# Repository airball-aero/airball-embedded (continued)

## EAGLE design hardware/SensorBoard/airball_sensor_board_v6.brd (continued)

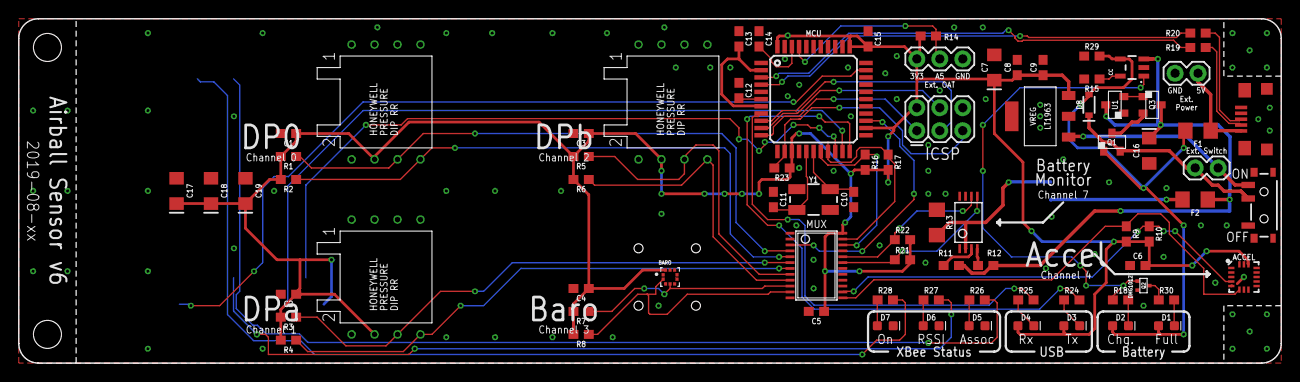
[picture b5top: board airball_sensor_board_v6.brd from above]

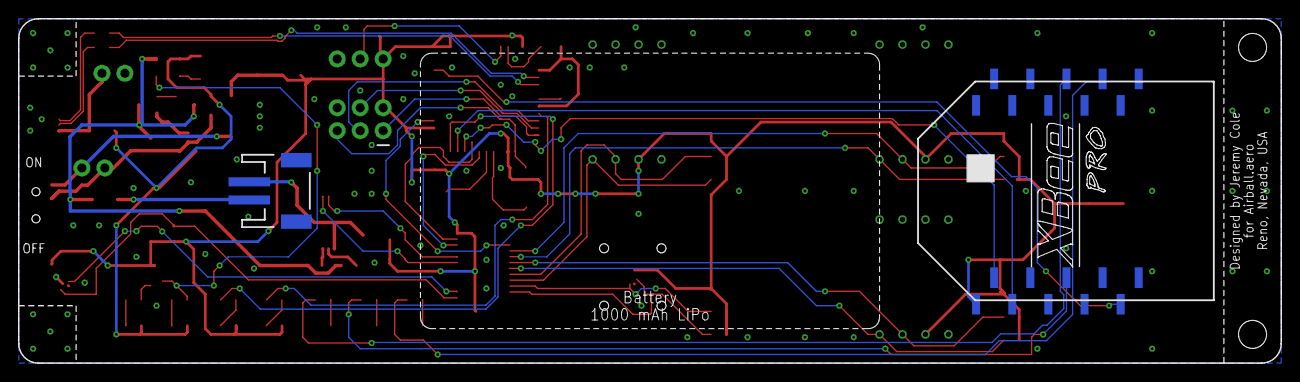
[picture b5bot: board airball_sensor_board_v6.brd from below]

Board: 2 copper layers, 139.7 x 38.1 mm, 83 parts (3 on the bottom side), 60 nets.

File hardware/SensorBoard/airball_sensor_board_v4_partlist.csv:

Partlist

Exported from airball_sensor_board_v4.brd at 2/25/20 10:12 PM

EAGLE Version 9.5.2 Copyright (c) 1988-2019 Autodesk, Inc.

Assembly variant: 

Part      Value               Package                Library             Position (mil)        Orientation

BARO                          ALLSENSORS_E1BD        airball             (1562.5 375)          R270
BM        DS2782              TSSOP8                 airball             (4725 825)            R0
C1        0.1uF               0603                   SparkFun-Capacitors (1175 1425)           R180
C2        0.1uF               0603                   SparkFun-Capacitors (1175 675)            R180
C3        0.1uF               0603                   SparkFun-Capacitors (2425 1425)           R180
C4        0.1uF               0603                   SparkFun-Capacitors (2425 675)            R180
C5        0.1uF               0603                   SparkFun-Capacitors (3475 225)            R180
C6        0.1uF               0603                   SparkFun-Capacitors (4875 425)            R180
C7        10uF                EIA3216                SparkFun-Capacitors (4250 1287.5)         R270
C8        1.0uF               0603                   SparkFun-Capacitors (4350 1287.5)         R90
C9        0.1uF               0603                   SparkFun-Capacitors (4462.5 1287.5)       R90
C10       22pF                0603                   SparkFun-Capacitors (3637.5 737.5)        R90
C11       22pF                0603                   SparkFun-Capacitors (3287.5 737.5)        R270
C12       1.0uF               0603                   SparkFun-Capacitors (3137.5 1187.5)       R270
C13       1.0uF               0603                   SparkFun-Capacitors (3137.5 1412.5)       R270
C14       0.1uF               0603                   SparkFun-Capacitors (3225 1412.5)         R270
C15       0.1uF               0603                   SparkFun-Capacitors (3700 1412.5)         R270
C16       10uF                EIA3216                SparkFun-Capacitors (4975 1037.5)         R90
C17       10uF                EIA3216                SparkFun-Capacitors (687.5 750)           R270
C18       10uF                EIA3216                SparkFun-Capacitors (837.5 750)           R270
C19       10uF                EIA3216                SparkFun-Capacitors (987.5 750)           R270
CC        MCP73831            SOT23-5                SparkFun-IC-Power   (4862.5 1175)         R0
D1                            LED-0603               SparkFun-LED        (5000 162.5)          R0
D2                            LED-0603               SparkFun-LED        (4800 162.5)          R0
D3                            LED-0603               SparkFun-LED        (4587.5 162.5)        R0
D4                            LED-0603               SparkFun-LED        (4387.5 162.5)        R0
D5                            LED-0603               SparkFun-LED        (4175 162.5)          R0
D6                            LED-0603               SparkFun-LED        (3975 162.5)          R0
D7                            LED-0603               SparkFun-LED        (3775 162.5)          R0
DP0                           ALLSENSORS_E1BD        airball             (1562.5 1125)         R270
DPA                           ALLSENSORS_E1BD        airball             (2812.5 1125)         R270
DPB                           ALLSENSORS_E1BD        airball             (2812.5 375)          R270
EXT_OAT                       1X03                   SparkFun-Connectors (3912.5 1325)         R0
EXT_POWER                     1X02                   SparkFun-Connectors (5137.5 1262.5)       R180
EXT_SW                        1X02                   SparkFun-Connectors (5125 850)            R0
F1        6V/0.5A             1206                   SparkFun-Fuses      (5137.5 1012.5)       R180
F2        6V/0.5A             1206                   SparkFun-Fuses      (5125 712.5)          R0
ICSP      AVR_SPI_PROG_3X2PTH 2X3                    SparkFun-Connectors (3912.5 1012.5)       R0
J1                            JST-2-SMD              SparkFun-Connectors (4350 750)            MR270
JP1       USB_MICROB_PLUG     USB_MICRO_B_TYCO       airball             (5437.5 1062.5)       R90
MCU       32U4                TQFP44                 jcole               (3462.5 1150)         R0
MUX                           TSSOP24                airball             (3475 425)            R270
OAT       TMP275              SOIC8                  airball             (5337.5 387.5)        R270
R1        4.7k                0603                   SparkFun-Resistors  (1175 1325)           R180
R2        4.7k                0603                   SparkFun-Resistors  (1175 1225)           R180
R3        4.7k                0603                   SparkFun-Resistors  (1175 575)            R180
R4        4.7k                0603                   SparkFun-Resistors  (1175 475)            R180
R5        4.7k                0603                   SparkFun-Resistors  (2425 1325)           R180
R6        4.7k                0603                   SparkFun-Resistors  (2425 1225)           R180
R7        4.7k                0603                   SparkFun-Resistors  (2425 575)            R180
R8        4.7k                0603                   SparkFun-Resistors  (2425 475)            R180
R9        4.7k                0603                   SparkFun-Resistors  (4825 562.5)          R270
R10       4.7k                0603                   SparkFun-Resistors  (4925 562.5)          R270
R11       1k                  0603                   SparkFun-Resistors  (4537.5 737.5)        R180
R12       470                 0603                   SparkFun-Resistors  (4537.5 662.5)        R180
R13       15m                 1206                   SparkFun-Resistors  (4937.5 837.5)        R0
R14       4.7k                0603                   SparkFun-Resistors  (3962.5 1425)         R180
R15       2.0k                0603                   SparkFun-Resistors  (4737.5 1200)         R90
R16       4.7k                0603                   SparkFun-Resistors  (3687.5 875)          R270
R17       4.7k                0603                   SparkFun-Resistors  (3787.5 875)          R270
R18       330                 0603                   SparkFun-Resistors  (4800 275)            R0
R19       22                  0603                   SparkFun-Resistors  (5137.5 1375)         R180
R20       22                  0603                   SparkFun-Resistors  (5137.5 1437.5)       R180
R21       4.7k                0603                   SparkFun-Resistors  (3850 450)            R0
R22       4.7k                0603                   SparkFun-Resistors  (3850 537.5)          R0
R23       10k                 0603                   SparkFun-Resistors  (3312.5 850)          R180
R24       330                 0603                   SparkFun-Resistors  (4587.5 275)          R0
R25       330                 0603                   SparkFun-Resistors  (4387.5 275)          R0
R26       330                 0603                   SparkFun-Resistors  (4175 275)            R0
R27       330                 0603                   SparkFun-Resistors  (3975 275)            R0
R28       330                 0603                   SparkFun-Resistors  (3775 275)            R0
S1                            SWITCH_SPST_SMD_A      SparkFun-Switches   (5425 687.5)          R270
VREG      LT1963              SOT223-3               airball             (4450 1075)           R90
XBEE      XBEE-PRO-SMD        XBEE-PRO-SMD           airball             (975 750)             MR90
Y1        8MHz                CRYSTAL-SMD-5X3.2-4PAD SparkFun-Clocks     (3462.5 737.5)        R0

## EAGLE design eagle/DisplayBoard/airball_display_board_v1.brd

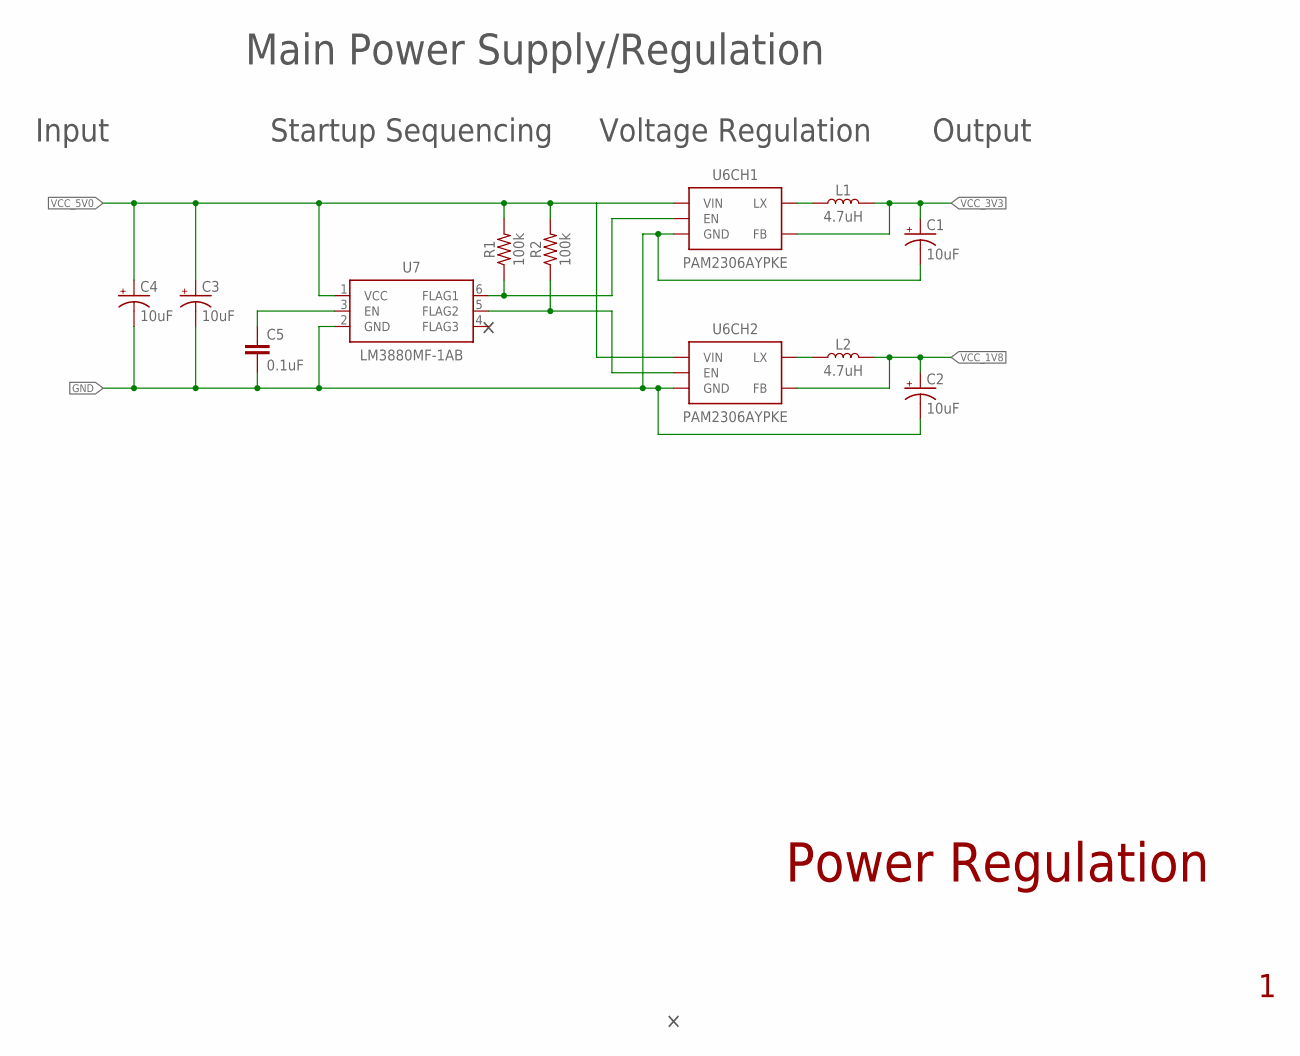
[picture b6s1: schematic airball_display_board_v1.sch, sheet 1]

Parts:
C1, C2, C3, C4: 10uF; EIA3216
C5: 0.1uF; 0603
L1, L2: 4.7uH; INDUCTOR_SMD_4X4MM
R1, R2: 100k; 0603
U6: PAM2306AYPKE; WDFN12
U7: LM3880MF-1AB; SOT23-6

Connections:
EN_1V8: R2.1, U6.12 (EN), U7.5 (FLAG2)
EN_3V3: R1.1, U6.6 (EN), U7.6 (FLAG1)
GND: C1.-, C2.-, C3.-, C4.-, C5.2, U6.3 (GND), U6.9 (GND), U7.2 (GND); also elsewhere on the board
unnamed: L1.1, U6.8 (LX)
unnamed: L2.1, U6.2 (LX)
unnamed: C5.1, U7.3 (EN)
VCC_1V8: C2.+, L2.2, U6.10 (FB); also elsewhere on the board
VCC_3V3: C1.+, L1.2, U6.4 (FB); also elsewhere on the board
VCC_5V0: C3.+, C4.+, R1.2, R2.2, U6.1 (VIN), U6.7 (VIN), U7.1 (VCC); also elsewhere on the board

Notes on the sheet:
Power Regulation
Main Power Supply/Regulation
Startup Sequencing
Voltage Regulation
Input
Output

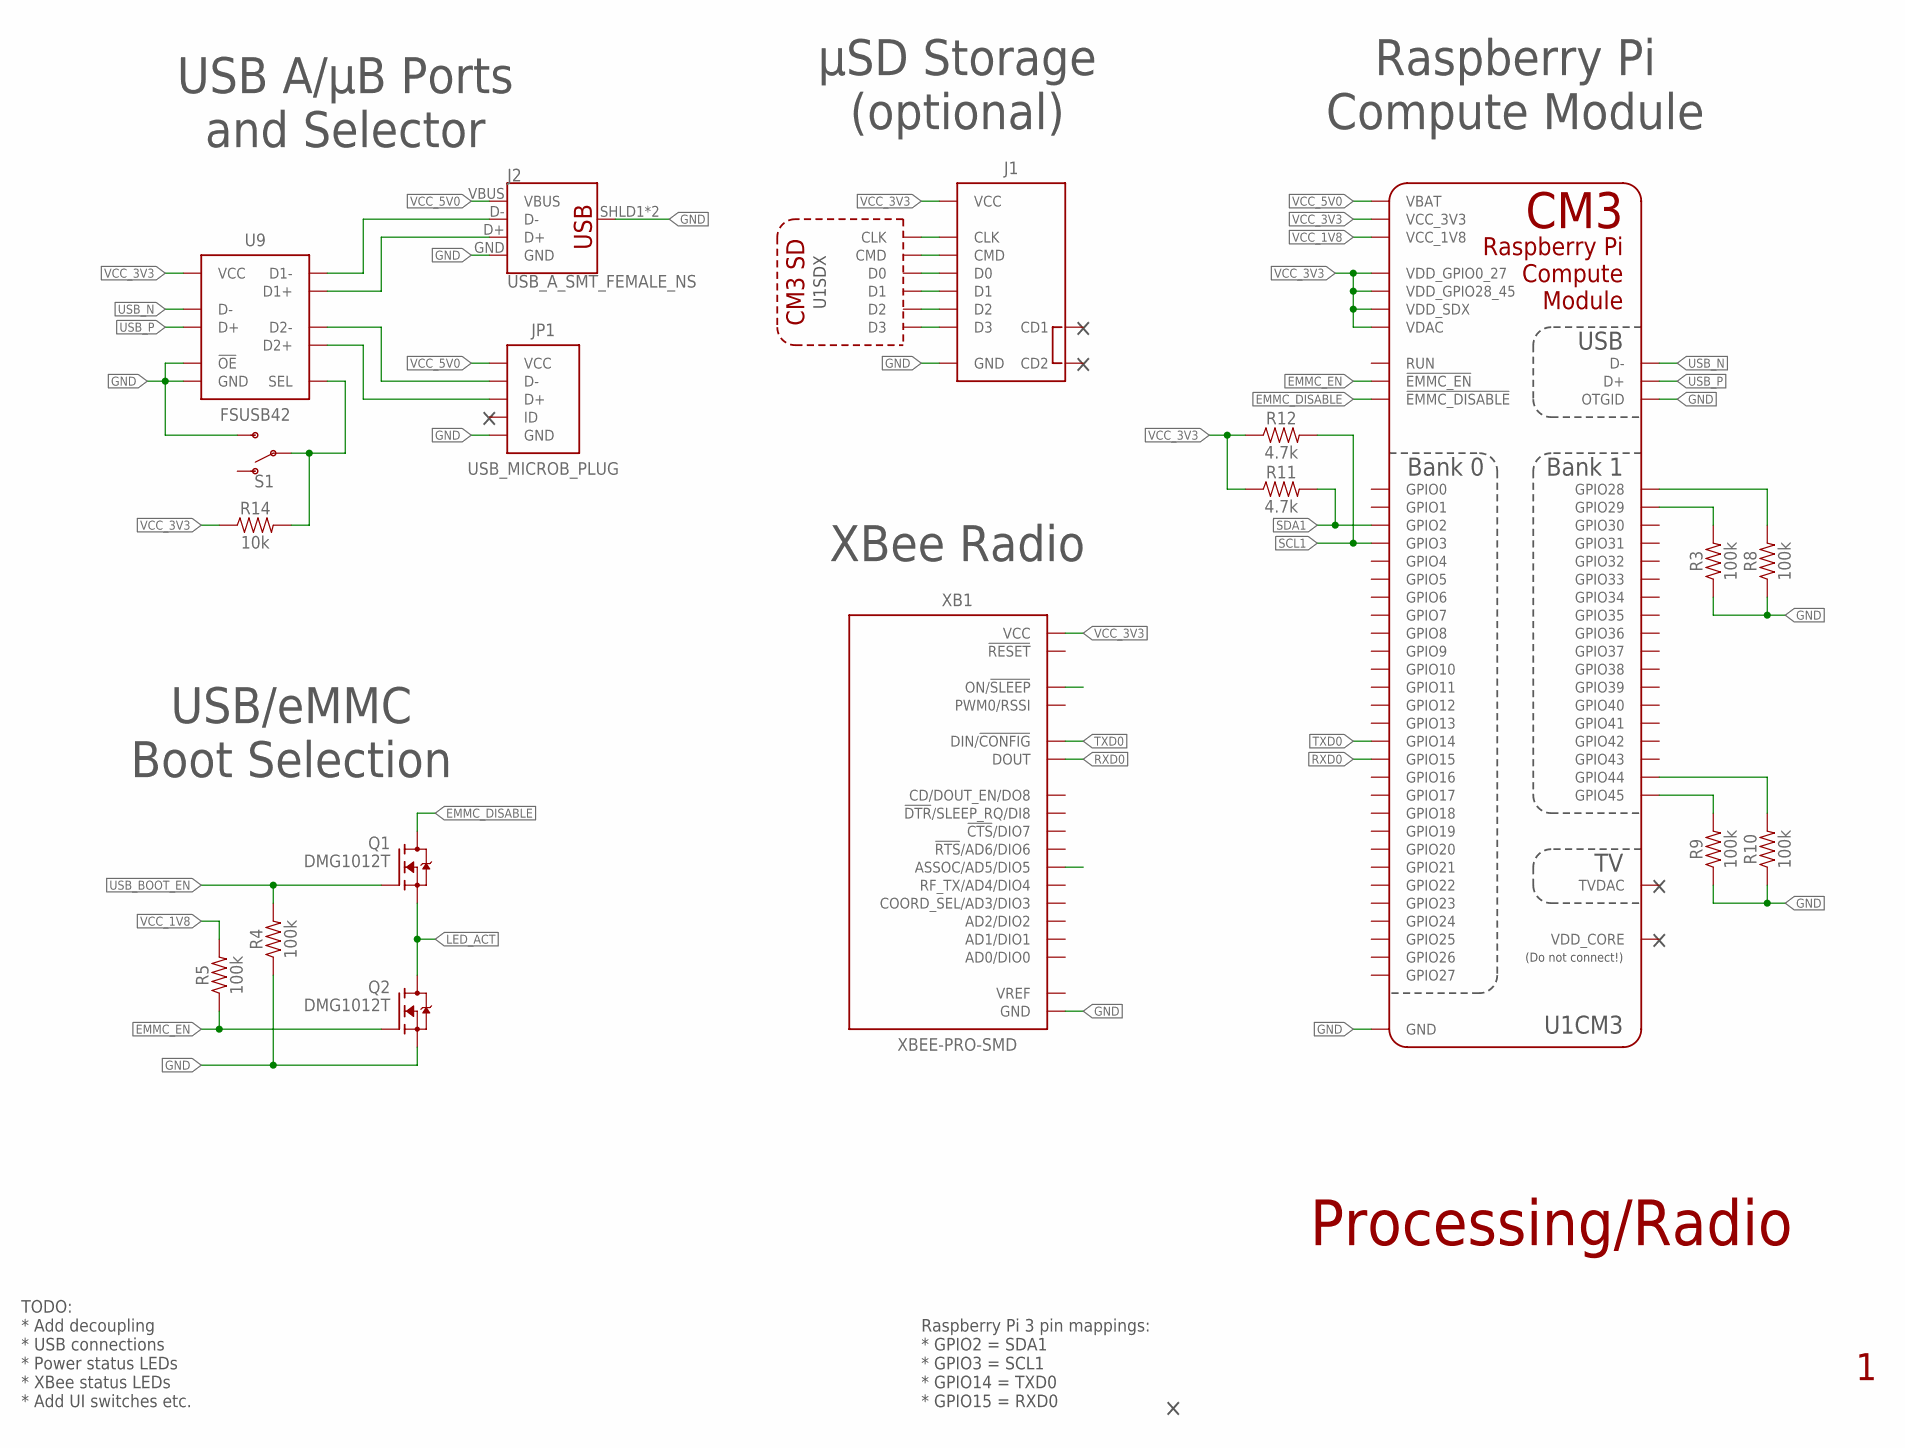
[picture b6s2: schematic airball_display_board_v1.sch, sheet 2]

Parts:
J1: MICRO-SD-SD4; MICRO-SD-SOCKET
J2: USB_A_SMT_FEMALE_NS; USB-A-S-NOSILK-FEMALE
JP1: USB_MICROB_PLUG; USB_MICRO_B_TYCO
Q1, Q2: DMG1012T; SOT523-3
R3, R4, R5, R8, R9, R10: 100k; 0603
R11, R12: 4.7k; 0603
R14: 10k; 0603
S1: SWITCH-SPDT-SMD-RIGHT-ANGLE; SWITCH_SPST_SMD_A
U1: RPI_CM3-TYCO1376408; RPI_CM_SOCKET
U9: FSUSB42; MSOP10
XB1: XBEE-PRO-SMD

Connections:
EMMC_DISABLE: Q1.2 (D), U1.2 (!EMMC_DISABLE)
EMMC_EN: Q2.1 (G), R5.1, U1.90 (!EMMC_EN)
GND: J1.6 (GND), J1.SH@1 (GND), J1.SH@2 (GND), J2.GND, J2.SHLD1 (SHIELD), J2.SHLD2 (SHIELD), JP1.5 (GND), JP1.SH@1 (GND), JP1.SH@2 (GND), JP1.SH@3 (GND), JP1.SH@4 (GND), Q2.3 (S), R3.1, R4.1, R8.1, R9.1, R10.1, S1.3 (S), U1.1 (GND), U1.7 (GND), U1.8 (GND), U1.13 (GND), U1.14 (GND), U1.19 (GND), U1.20 (GND), U1.25 (GND), U1.26 (GND), U1.31 (GND), U1.32 (GND), U1.37 (GND), U1.38 (GND), U1.43 (GND), U1.44 (GND), U1.49 (GND), U1.50 (GND), U1.55 (GND), U1.56 (GND), U1.61 (GND), U1.62 (GND), U1.67 (GND), U1.68 (GND), U1.73 (GND), U1.74 (GND), U1.79 (GND), U1.80 (GND), U1.85 (GND), U1.86 (GND), U1.91 (GND), U1.92 (GND), U1.97 (GND), U1.98 (GND), U1.103 (GND), U1.104 (GND), U1.109 (GND), U1.110 (GND), U1.115 (GND), U1.116 (GND), U1.121 (GND), U1.122 (GND), U1.127 (GND), U1.133 (GND), U1.134 (GND), U1.139 (GND), U1.140 (GND), U1.145 (GND), U1.146 (GND), U1.151 (GND), U1.152 (GND), U1.157 (GND), U1.163 (GND), U1.164 (GND), U1.168 (OTGID), U1.169 (GND), U1.170 (GND), U1.181 (GND), U1.182 (GND), U1.187 (GND), U1.188 (GND), U1.195 (GND), U1.196 (GND), U9.5 (GND), U9.10 (!OE), XB1.10 (GND); also elsewhere on the board
LED_ACT: Q1.3 (S), Q2.2 (D)
unnamed: J1.5 (CLK), U1.10 (CLK)
unnamed: J1.3 (CMD), U1.12 (CMD)
unnamed: J1.7 (D0), U1.16 (D0)
unnamed: J1.8 (D1), U1.18 (D1)
unnamed: J1.1 (D2), U1.22 (D2)
unnamed: J1.2 (D3), U1.24 (D3)
unnamed: R3.2, U1.30 (GPIO29)
unnamed: R8.2, U1.28 (GPIO28)
unnamed: R9.2, U1.84 (GPIO45)
unnamed: R10.2, U1.82 (GPIO44)
unnamed: R14.2, S1.2, U9.2 (SEL)
RXD0: U1.53 (GPIO15), XB1.2 (DOUT)
SCL1: R12.2, U1.11 (GPIO3); also elsewhere on the board
SDA1: R11.2, U1.9 (GPIO2); also elsewhere on the board
TXD0: U1.51 (GPIO14), XB1.3 (DIN/!CONFIG)
USB_A_N: J2.D-, U9.6 (D1-)
USB_A_P: J2.D+, U9.7 (D1+)
USB_BOOT_EN: Q1.1 (G), R4.2
USB_B_N: JP1.2 (D-), U9.8 (D2-)
USB_B_P: JP1.3 (D+), U9.9 (D2+)
USB_N: U1.167 (D-), U9.4 (D-)
USB_P: U1.165 (D+), U9.3 (D+)
VCC_1V8: R5.2, U1.183 (VCC_1V8), U1.184 (VCC_1V8), U1.185 (VCC_1V8), U1.186 (VCC_1V8); also elsewhere on the board
VCC_3V3: J1.4 (VCC), R11.1, R12.1, R14.1, U1.4 (VDD_SDX), U1.6 (VDD_SDX), U1.39 (VDD_GPIO0_27), U1.40 (VDD_GPIO0_27), U1.41 (VDD_GPIO28_45), U1.42 (VDD_GPIO28_45), U1.189 (VDAC), U1.190 (VDAC), U1.191 (VCC_3V3), U1.192 (VCC_3V3), U1.193 (VCC_3V3), U1.194 (VCC_3V3), U9.1 (VCC), XB1.1 (VCC); also elsewhere on the board
VCC_5V0: J2.VBUS, JP1.1 (VCC), U1.197 (VBAT), U1.198 (VBAT), U1.199 (VBAT), U1.200 (VBAT); also elsewhere on the board
VDD_CORE: U1.179 (VDD_CORE)

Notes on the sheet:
Raspberry Pi 3 pin mappings: * GPIO2 = SDA1 * GPIO3 = SCL1 * GPIO14 = TXD0 * GPIO15 = RXD0
USB/eMMC Boot Selection
Processing/Radio
USB A/µB Ports and Selector
µSD Storage (optional)
XBee Radio
Raspberry Pi Compute Module
TODO: * Add decoupling * USB connections * Power status LEDs * XBee status LEDs * Add UI switches etc.

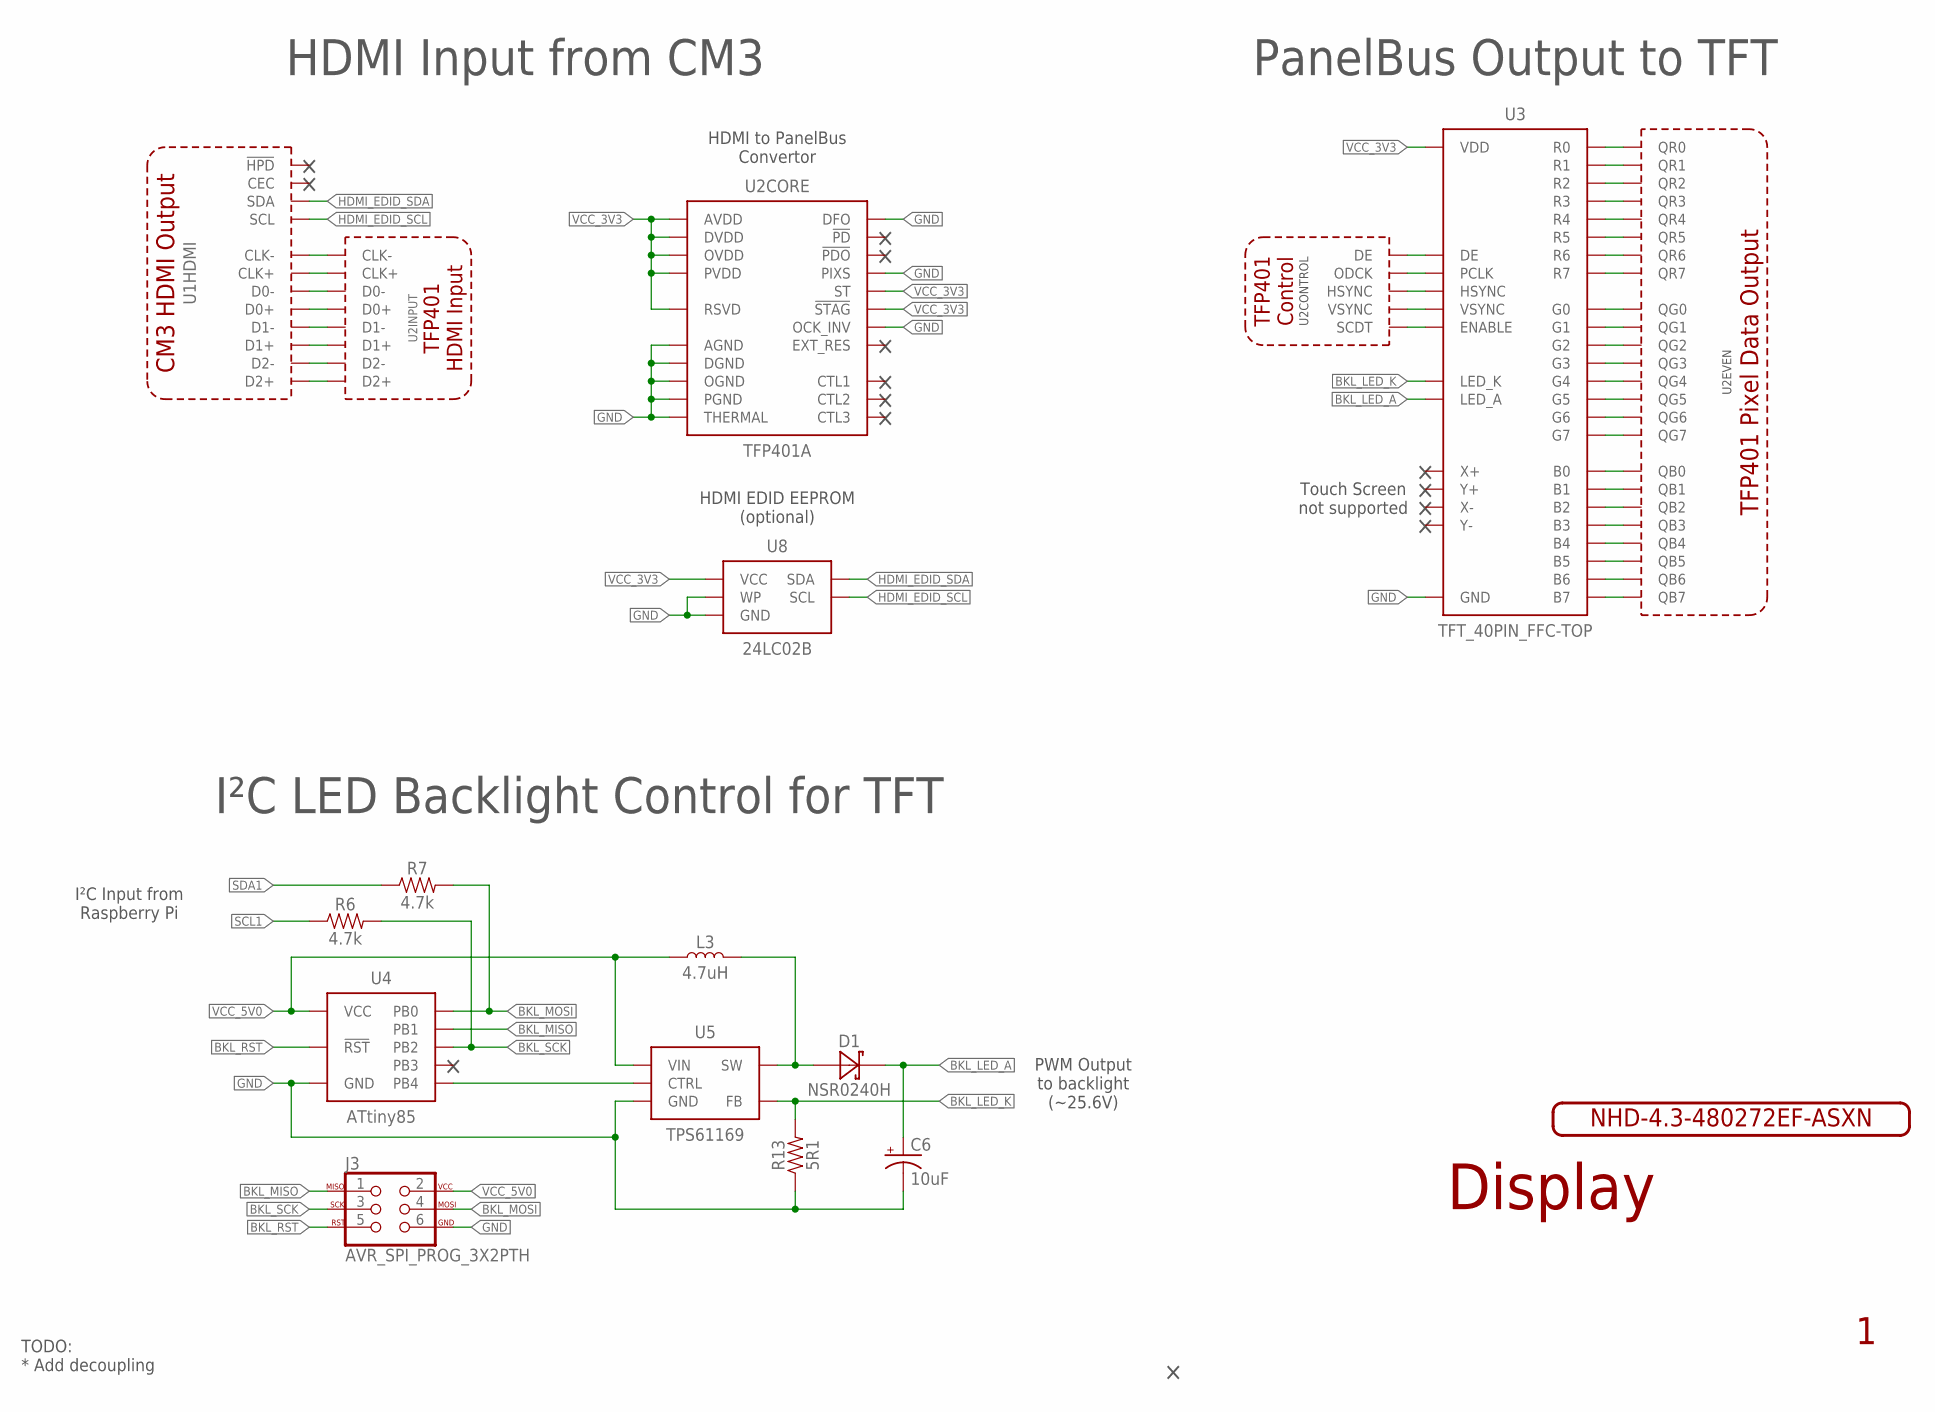
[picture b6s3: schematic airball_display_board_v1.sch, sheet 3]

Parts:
C6: 10uF; EIA3216
D1: NSR0240H; SOD323
J3: AVR_SPI_PROG_3X2PTH; 2X3
L3: 4.7uH; INDUCTOR_SMD_4X4MM
R6, R7: 4.7k; 0603
R13: 5R1; 0603
U1: RPI_CM3-TYCO1376408; RPI_CM_SOCKET
U2: TFP401A; TQFP100_POWER_LITE
U3: TFT_40PIN_FFC-TOP; HIROSE_FFC40_FH12-40S-0.5SH
U4: ATtiny85; SOIC8
U5: TPS61169; SOT353-5
U8: 24LC02B; SOT23-5
U$4: NHD-4.3-480272EF-ASXN

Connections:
B0: U2.10 (QB0), U3.20 (B0)
B1: U2.11 (QB1), U3.19 (B1)
B2: U2.12 (QB2), U3.18 (B2)
B3: U2.13 (QB3), U3.17 (B3)
B4: U2.14 (QB4), U3.16 (B4)
B5: U2.15 (QB5), U3.15 (B5)
B6: U2.16 (QB6), U3.14 (B6)
B7: U2.17 (QB7), U3.13 (B7)
BKL_LED_A: C6.+, D1.K (C), U3.39 (LED_A)
BKL_LED_K: R13.2, U3.40 (LED_K), U5.3 (FB)
BKL_MISO: J3.1, U4.6 (PB1)
BKL_MOSI: J3.4, R7.2, U4.5 (PB0)
BKL_RST: J3.5, U4.1 (!RST)
BKL_SCK: J3.3, R6.2, U4.7 (PB2)
DE: U2.46 (DE), U3.7 (DE)
G0: U2.20 (QG0), U3.28 (G0)
G1: U2.21 (QG1), U3.27 (G1)
G2: U2.22 (QG2), U3.26 (G2)
G3: U2.23 (QG3), U3.25 (G3)
G4: U2.24 (QG4), U3.24 (G4)
G5: U2.25 (QG5), U3.23 (G5)
G6: U2.26 (QG6), U3.22 (G6)
G7: U2.27 (QG7), U3.21 (G7)
GND: C6.-, J3.6, R13.1, U2.1 (DFO), U2.4 (PIXS), U2.5 (DGND), U2.19 (OGND), U2.28 (OGND), U2.39 (DGND), U2.45 (OGND), U2.58 (OGND), U2.68 (DGND), U2.76 (OGND), U2.79 (AGND), U2.83 (AGND), U2.87 (AGND), U2.89 (AGND), U2.92 (AGND), U2.98 (PGND), U2.100 (OCK_INV), U2.TH21 (THERMAL), U2.TH22 (THERMAL), U2.TH23 (THERMAL), U2.TH24 (THERMAL), U2.TH25 (THERMAL), U2.TH30 (THERMAL), U2.TH34 (THERMAL), U2.TH39 (THERMAL), U2.TH43 (THERMAL), U2.TH48 (THERMAL), U2.TH52 (THERMAL), U2.TH57 (THERMAL), U2.TH58 (THERMAL), U2.TH59 (THERMAL), U2.TH60 (THERMAL), U2.TH61 (THERMAL), U2.THA (THERMAL), U2.THB (THERMAL), U3.5 (GND), U3.12 (GND), U3.38 (GND), U4.4 (GND), U5.2 (GND), U8.2 (GND), U8.5 (WP); also elsewhere on the board
HDMI_EDID_SCL: U1.175 (SCL), U8.1 (SCL)
HDMI_EDID_SDA: U1.173 (SDA), U8.3 (SDA)
HSYNC: U2.48 (HSYNC), U3.9 (HSYNC)
unnamed: U1.131 (D2+), U2.80 (D2+)
unnamed: U1.129 (D2-), U2.81 (D2-)
unnamed: U1.125 (D1+), U2.85 (D1+)
unnamed: U1.123 (D1-), U2.86 (D1-)
unnamed: U1.119 (D0+), U2.90 (D0+)
unnamed: U1.117 (D0-), U2.91 (D0-)
unnamed: U1.113 (CLK+), U2.93 (CLK+)
unnamed: U1.111 (CLK-), U2.94 (CLK-)
unnamed: U4.3 (PB4), U5.4 (CTRL)
unnamed: D1.A, L3.2, U5.1 (SW)
PCLK: U2.44 (ODCK), U3.11 (PCLK)
R0: U2.30 (QR0), U3.36 (R0)
R1: U2.31 (QR1), U3.35 (R1)
R2: U2.32 (QR2), U3.34 (R2)
R3: U2.33 (QR3), U3.33 (R3)
R4: U2.34 (QR4), U3.32 (R4)
R5: U2.35 (QR5), U3.31 (R5)
R6: U2.36 (QR6), U3.30 (R6)
R7: U2.37 (QR7), U3.29 (R7)
SCDT: U2.8 (SCDT), U3.10 (ENABLE)
SCL1: R6.1; also elsewhere on the board
SDA1: R7.1; also elsewhere on the board
VCC_3V3: U2.3 (ST), U2.6 (DVDD), U2.7 (!STAG), U2.18 (OVDD), U2.29 (OVDD), U2.38 (DVDD), U2.43 (OVDD), U2.57 (OVDD), U2.67 (DVDD), U2.78 (OVDD), U2.82 (AVDD), U2.84 (AVDD), U2.88 (AVDD), U2.95 (AVDD), U2.97 (PVDD), U2.99 (RSVD), U3.37 (VDD), U8.4 (VCC); also elsewhere on the board
VCC_5V0: J3.2, L3.1, U4.8 (VCC), U5.5 (VIN); also elsewhere on the board
VDD_CORE: U1.179 (VDD_CORE)
VSYNC: U2.47 (VSYNC), U3.8 (VSYNC)

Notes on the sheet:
I²C LED Backlight Control for TFT
Display
PanelBus Output to TFT
HDMI Input from CM3
TODO: * Add decoupling
Touch Screen not supported
PWM Output to backlight (~25.6V)
I²C Input from Raspberry Pi
HDMI EDID EEPROM (optional)
HDMI to PanelBus Convertor

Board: 2 copper layers, 42 parts (0 on the bottom side), 81 nets, no tracks yet.

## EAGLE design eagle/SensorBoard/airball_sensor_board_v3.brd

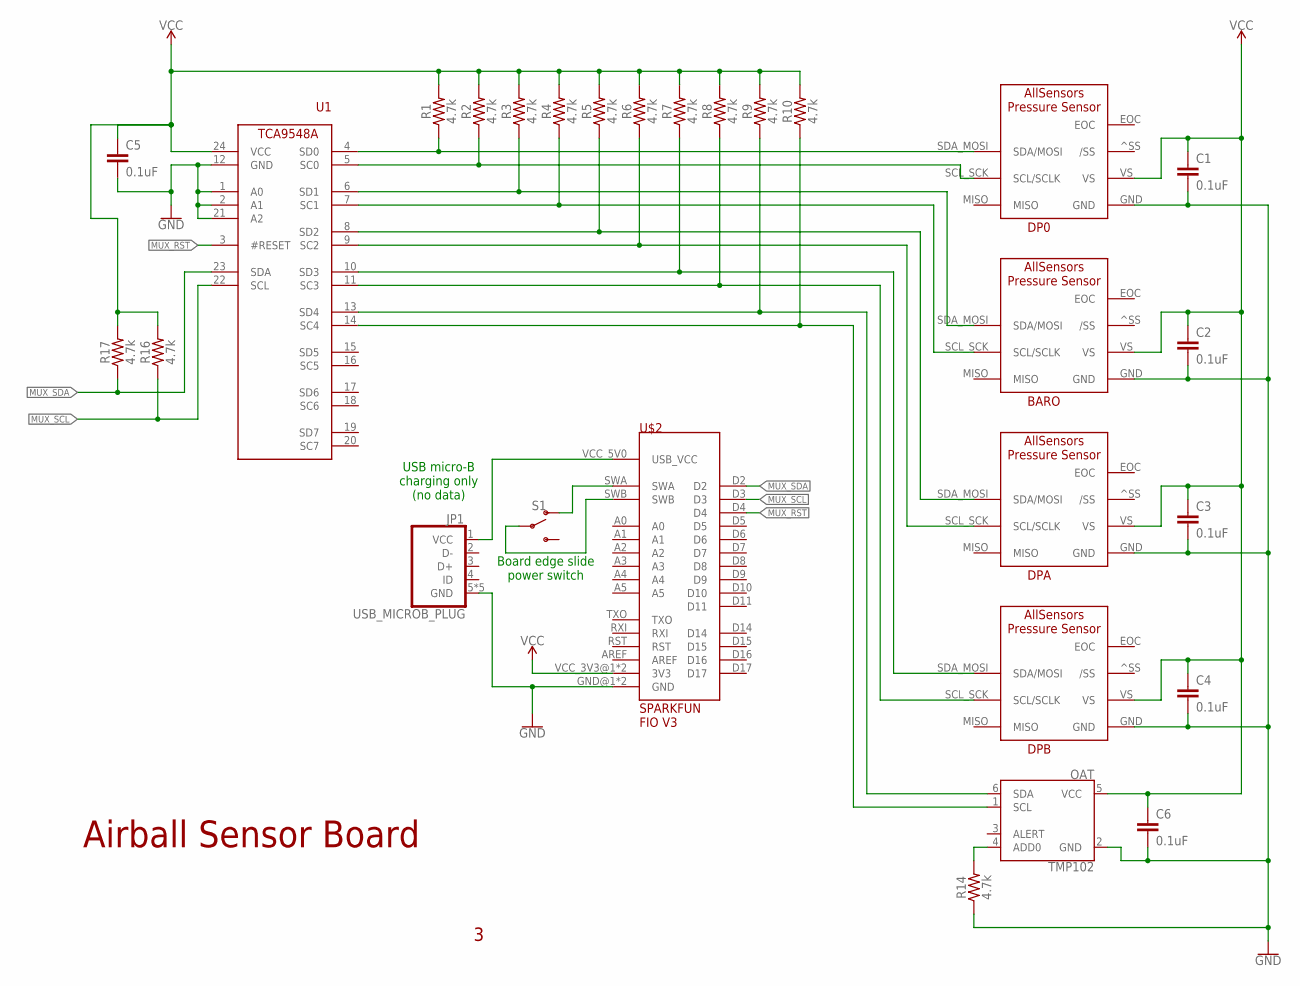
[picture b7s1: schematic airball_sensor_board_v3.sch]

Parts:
BARO: ALL_SENSORS_DLHR_E1ND; ALL_SENSORS_E1BD_8PIN_THRU
C1, C2, C3, C4, C5, C6: 0.1uF; 0603
DP0: ALL_SENSORS_DLHR_E1ND; ALL_SENSORS_E1BD_8PIN_THRU
DPA: ALL_SENSORS_DLHR_E1ND; ALL_SENSORS_E1BD_8PIN_THRU
DPB: ALL_SENSORS_DLHR_E1ND; ALL_SENSORS_E1BD_8PIN_THRU
JP1: USB_MICROB_PLUG; USB_MICRO_B_TYCO
OAT: TMP102; SOT563
R1, R2, R3, R4, R5, R6, R7, R8, R9, R10, R14, R16, R17: 4.7k; 0603
S1: SWITCH-SPDT-SMD-RIGHT-ANGLE; SWITCH_SPST_SMD_A
U1: TCA9548ATSSOP24; TSSOP24
U$2: SPARKFUN_FIO_V3

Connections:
GND: BARO.GND, C1.2, C2.2, C3.2, C4.2, C5.2, C6.2, DP0.GND, DPA.GND, DPB.GND, JP1.5 (GND), JP1.SH@1 (GND), JP1.SH@2 (GND), JP1.SH@3 (GND), JP1.SH@4 (GND), OAT.2 (GND), R14.1, U1.1 (A0), U1.2 (A1), U1.12 (GND), U1.21 (A2), U$2.GND@1 (GND), U$2.GND@2 (GND)
MUX_RST: U1.3 (#RESET), U$2.D4
MUX_SCL: R16.1, U1.22 (SCL), U$2.D3
MUX_SDA: R17.1, U1.23 (SDA), U$2.D2
OAT_ADD0: OAT.4 (ADD0), R14.2
SCL_BARO: BARO.SCL_SCK (SCL/SCLK), R4.1, U1.7 (SC1)
SCL_DP0: DP0.SCL_SCK (SCL/SCLK), R2.1, U1.5 (SC0)
SCL_DPA: DPA.SCL_SCK (SCL/SCLK), R6.1, U1.9 (SC2)
SCL_DPB: DPB.SCL_SCK (SCL/SCLK), R8.1, U1.11 (SC3)
SCL_OAT: OAT.1 (SCL), R10.1, U1.14 (SC4)
SDA_BARO: BARO.SDA_MOSI (SDA/MOSI), R3.1, U1.6 (SD1)
SDA_DP0: DP0.SDA_MOSI (SDA/MOSI), R1.1, U1.4 (SD0)
SDA_DPA: DPA.SDA_MOSI (SDA/MOSI), R5.1, U1.8 (SD2)
SDA_DPB: DPB.SDA_MOSI (SDA/MOSI), R7.1, U1.10 (SD3)
SDA_OAT: OAT.6 (SDA), R9.1, U1.13 (SD4)
SWA: S1.1 (O), U$2.SWA
SWB: S1.2, U$2.SWB
VCC_3V3: BARO.VS, C1.1, C2.1, C3.1, C4.1, C5.1, C6.1, DP0.VS, DPA.VS, DPB.VS, OAT.5 (VCC), R1.2, R2.2, R3.2, R4.2, R5.2, R6.2, R7.2, R8.2, R9.2, R10.2, R16.2, R17.2, U1.24 (VCC), U$2.VCC_3V3@1 (3V3), U$2.VCC_3V3@2 (3V3)
VCC_USB: JP1.1 (VCC), U$2.VCC_5V0 (USB_VCC)

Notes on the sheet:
USB micro-B charging only (no data)
Board edge slide power switch
Airball Sensor Board

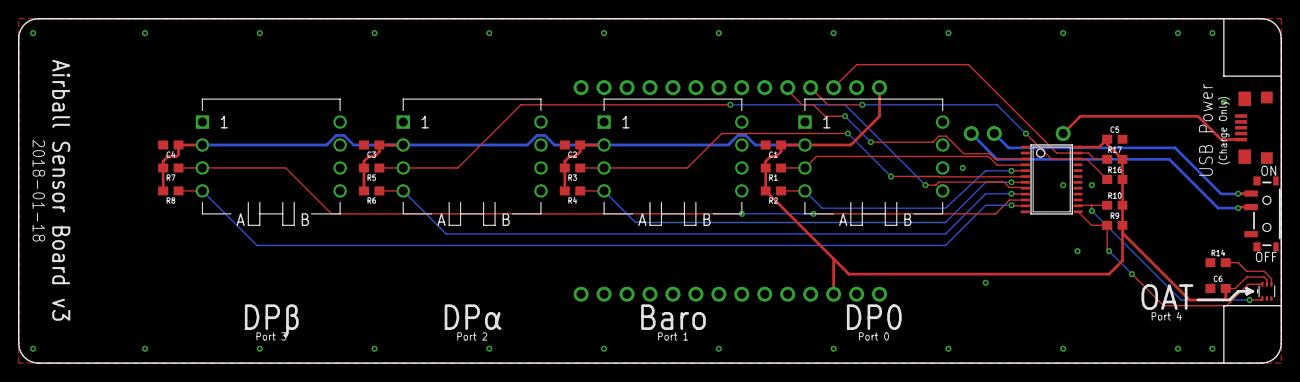
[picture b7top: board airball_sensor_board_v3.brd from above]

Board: 2 copper layers, 139.7 x 38.1 mm, 28 parts (1 on the bottom side), 19 nets.
